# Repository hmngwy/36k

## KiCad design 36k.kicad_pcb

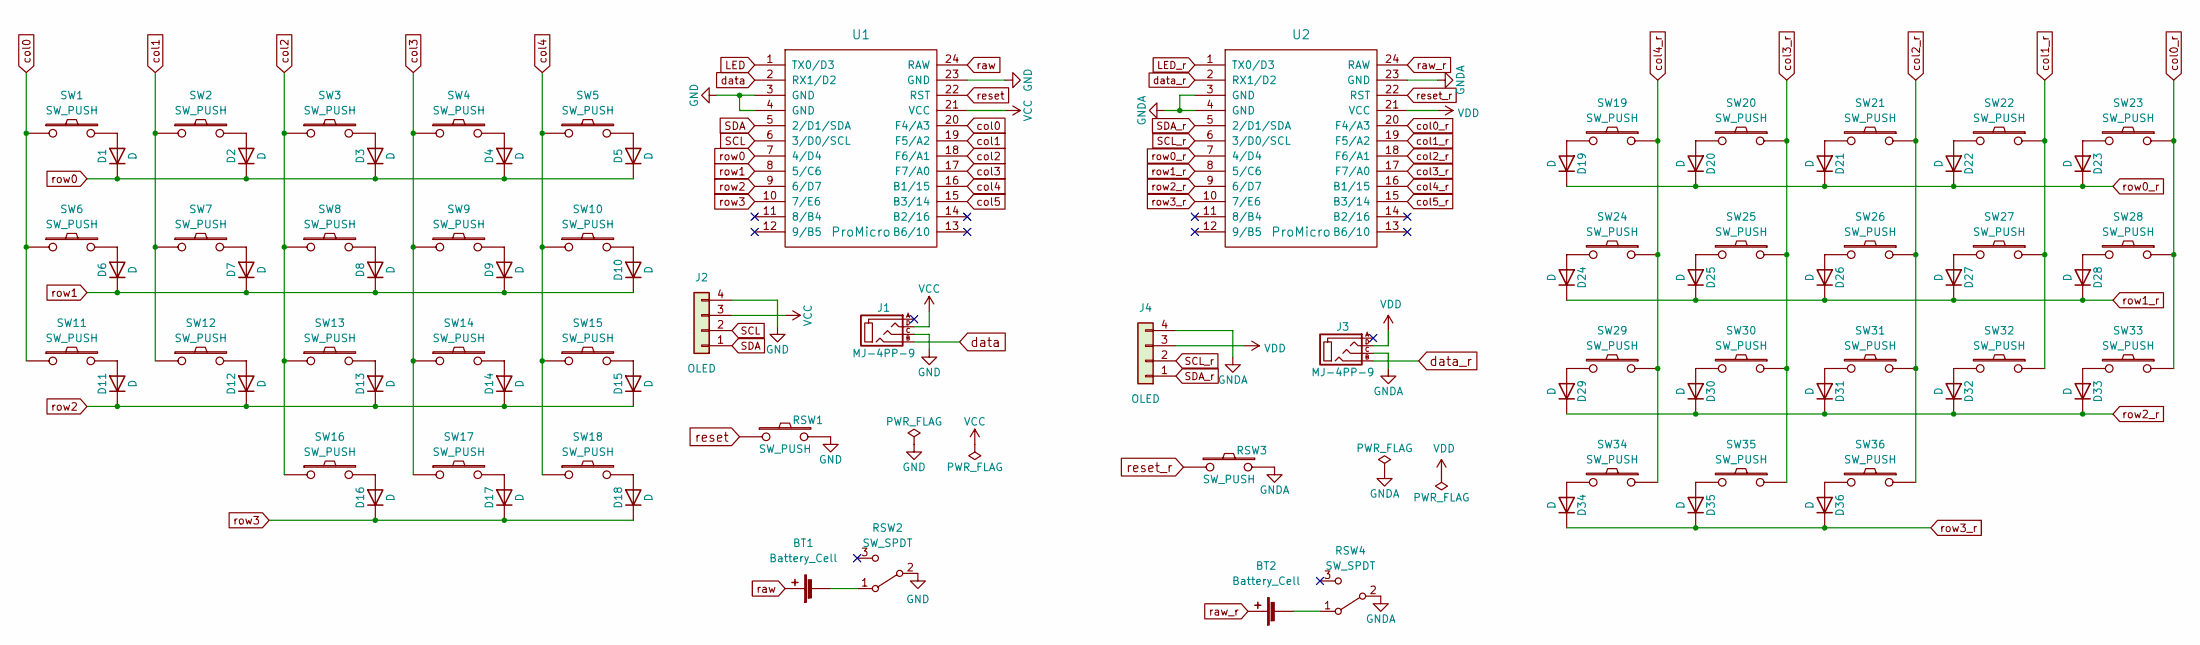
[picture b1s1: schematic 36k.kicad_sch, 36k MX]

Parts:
BT1, BT2: Battery_Cell; Battery_pads
D1, D2, D3, D4, D5, D6, D7, D8, D9, D10, D11, D12, D13, D14, D15, D16, D17, D18, D19, D20, D21, D22, D23, D24, D25, D26, D27, D28, D29, D30, D31, D32, D33, D34, D35, D36: D; D3_SMD_v2
J1, J3: MJ-4PP-9; MJ-4PP-9_1side
J2, J4: OLED; OLED_1side
RSW1, RSW3: SW_PUSH; ResetSW_1side
RSW2, RSW4: SW_SPDT; SW_CuK_OS102011MA1QN1_SPDT_Angled
SW1, SW2, SW3, SW4, SW5, SW6, SW7, SW8, SW9, SW10, SW11, SW12, SW13, SW14, SW15, SW16, SW17, SW19, SW20, SW21, SW22, SW23, SW24, SW25, SW26, SW27, SW28, SW29, SW30, SW31, SW32, SW33, SW35, SW36: SW_PUSH; CherryMX_Hotswap
SW18, SW34: SW_PUSH; CherryMX_Hotswap_1.5u
U1, U2: ProMicro; ProMicro_v3

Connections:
GND: J1.C, J2.4, RSW1.2, RSW2.2 (B), U1.3 (GND), U1.4 (GND), U1.23 (GND)
GNDA: J3.C, J4.4, RSW3.2, RSW4.2 (B), U2.3 (GND), U2.4 (GND), U2.23 (GND)
LED: U1.1 (TX0/D3)
LED_r: U2.1 (TX0/D3)
unnamed: BT1.2 (-), RSW2.1 (A)
unnamed: BT2.2 (-), RSW4.1 (A)
unnamed: D1.2 (A), SW1.2
unnamed: D2.2 (A), SW2.2
unnamed: D3.2 (A), SW3.2
unnamed: D4.2 (A), SW4.2
unnamed: D5.2 (A), SW5.2
unnamed: D6.2 (A), SW6.2
unnamed: D7.2 (A), SW7.2
unnamed: D8.2 (A), SW8.2
unnamed: D9.2 (A), SW9.2
unnamed: D10.2 (A), SW10.2
unnamed: D11.2 (A), SW11.2
unnamed: D12.2 (A), SW12.2
unnamed: D13.2 (A), SW13.2
unnamed: D14.2 (A), SW14.2
unnamed: D15.2 (A), SW15.2
unnamed: D16.2 (A), SW16.2
unnamed: D17.2 (A), SW17.2
unnamed: D18.2 (A), SW18.2
unnamed: D19.2 (A), SW19.2
unnamed: D20.2 (A), SW20.2
unnamed: D21.2 (A), SW21.2
unnamed: D22.2 (A), SW22.2
unnamed: D23.2 (A), SW23.2
unnamed: D24.2 (A), SW24.2
unnamed: D25.2 (A), SW25.2
unnamed: D26.2 (A), SW26.2
unnamed: D27.2 (A), SW27.2
unnamed: D28.2 (A), SW28.2
unnamed: D29.2 (A), SW29.2
unnamed: D30.2 (A), SW30.2
unnamed: D31.2 (A), SW31.2
unnamed: D32.2 (A), SW32.2
unnamed: D33.2 (A), SW33.2
unnamed: D34.2 (A), SW34.2
unnamed: D35.2 (A), SW35.2
unnamed: D36.2 (A), SW36.2
SCL: J2.2, U1.6 (3/D0/SCL)
SCL_r: J4.2, U2.6 (3/D0/SCL)
SDA: J2.1, U1.5 (2/D1/SDA)
SDA_r: J4.1, U2.5 (2/D1/SDA)
VCC: J1.D, J2.3, U1.21 (VCC)
VDD: J3.D, J4.3, U2.21 (VCC)
col0: SW1.1, SW6.1, SW11.1, U1.20 (F4/A3)
col0_r: SW23.1, SW28.1, SW33.1, U2.20 (F4/A3)
col1: SW2.1, SW7.1, SW12.1, U1.19 (F5/A2)
col1_r: SW22.1, SW27.1, SW32.1, U2.19 (F5/A2)
col2: SW3.1, SW8.1, SW13.1, SW16.1, U1.18 (F6/A1)
col2_r: SW21.1, SW26.1, SW31.1, SW36.1, U2.18 (F6/A1)
col3: SW4.1, SW9.1, SW14.1, SW17.1, U1.17 (F7/A0)
col3_r: SW20.1, SW25.1, SW30.1, SW35.1, U2.17 (F7/A0)
col4: SW5.1, SW10.1, SW15.1, SW18.1, U1.16 (B1/15)
col4_r: SW19.1, SW24.1, SW29.1, SW34.1, U2.16 (B1/15)
col5: U1.15 (B3/14)
col5_r: U2.15 (B3/14)
data: J1.B, U1.2 (RX1/D2)
data_r: J3.B, U2.2 (RX1/D2)
raw: BT1.1 (+), U1.24 (RAW)
raw_r: BT2.1 (+), U2.24 (RAW)
reset: RSW1.1, U1.22 (RST)
reset_r: RSW3.1, U2.22 (RST)
row0: D1.1 (K), D2.1 (K), D3.1 (K), D4.1 (K), D5.1 (K), U1.7 (4/D4)
row0_r: D19.1 (K), D20.1 (K), D21.1 (K), D22.1 (K), D23.1 (K), U2.7 (4/D4)
row1: D6.1 (K), D7.1 (K), D8.1 (K), D9.1 (K), D10.1 (K), U1.8 (5/C6)
row1_r: D24.1 (K), D25.1 (K), D26.1 (K), D27.1 (K), D28.1 (K), U2.8 (5/C6)
row2: D11.1 (K), D12.1 (K), D13.1 (K), D14.1 (K), D15.1 (K), U1.9 (6/D7)
row2_r: D29.1 (K), D30.1 (K), D31.1 (K), D32.1 (K), D33.1 (K), U2.9 (6/D7)
row3: D16.1 (K), D17.1 (K), D18.1 (K), U1.10 (7/E6)
row3_r: D34.1 (K), D35.1 (K), D36.1 (K), U2.10 (7/E6)

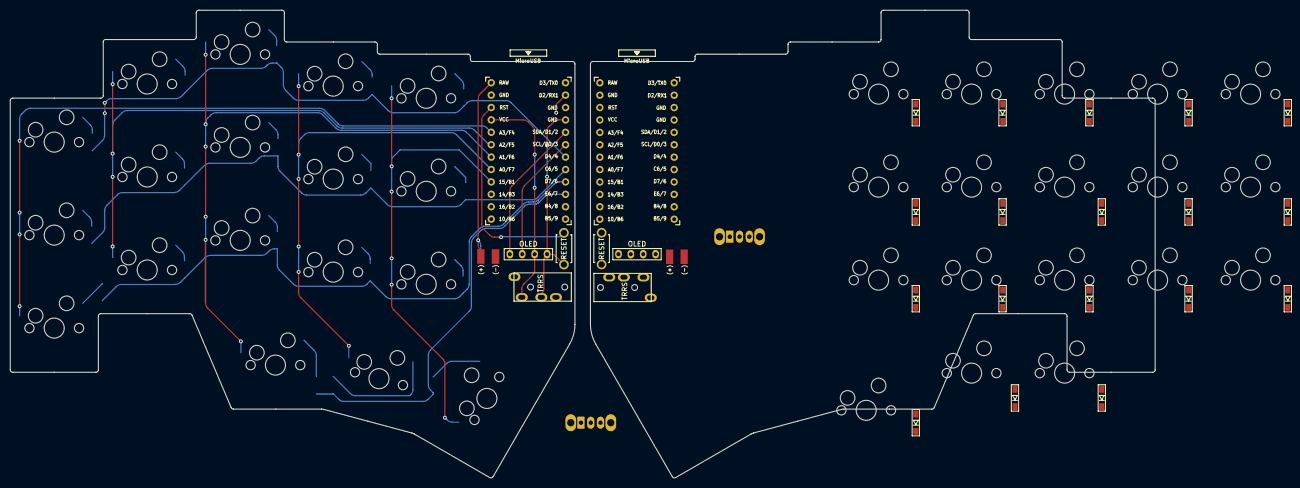
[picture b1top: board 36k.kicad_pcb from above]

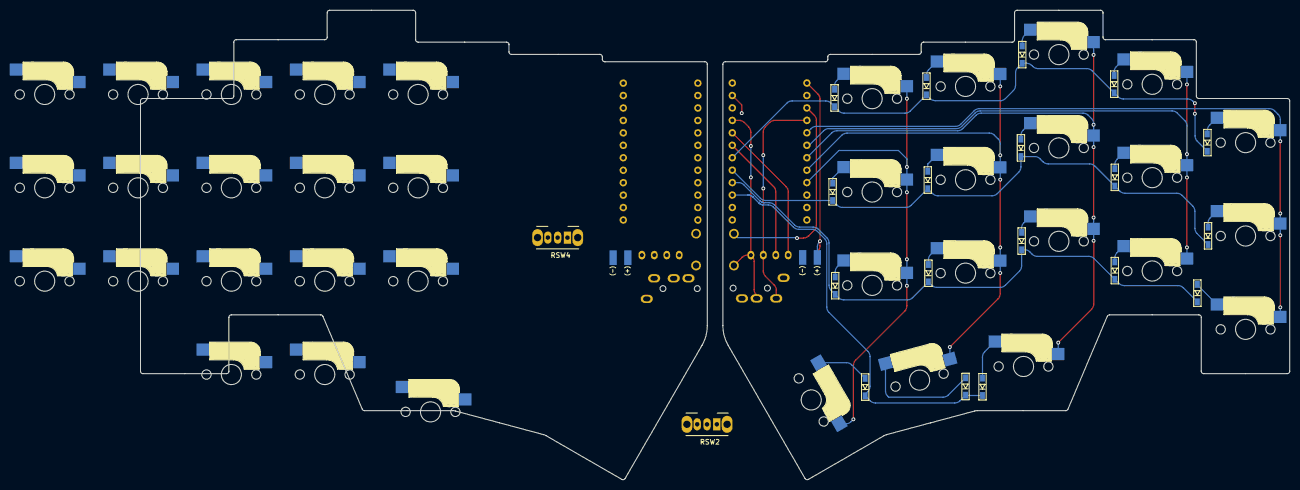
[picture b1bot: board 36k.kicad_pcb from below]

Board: 2 copper layers, 234.5 x 95.8 mm, 84 parts (22 on the bottom side), 70 nets.

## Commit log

2021-12-04 initial
